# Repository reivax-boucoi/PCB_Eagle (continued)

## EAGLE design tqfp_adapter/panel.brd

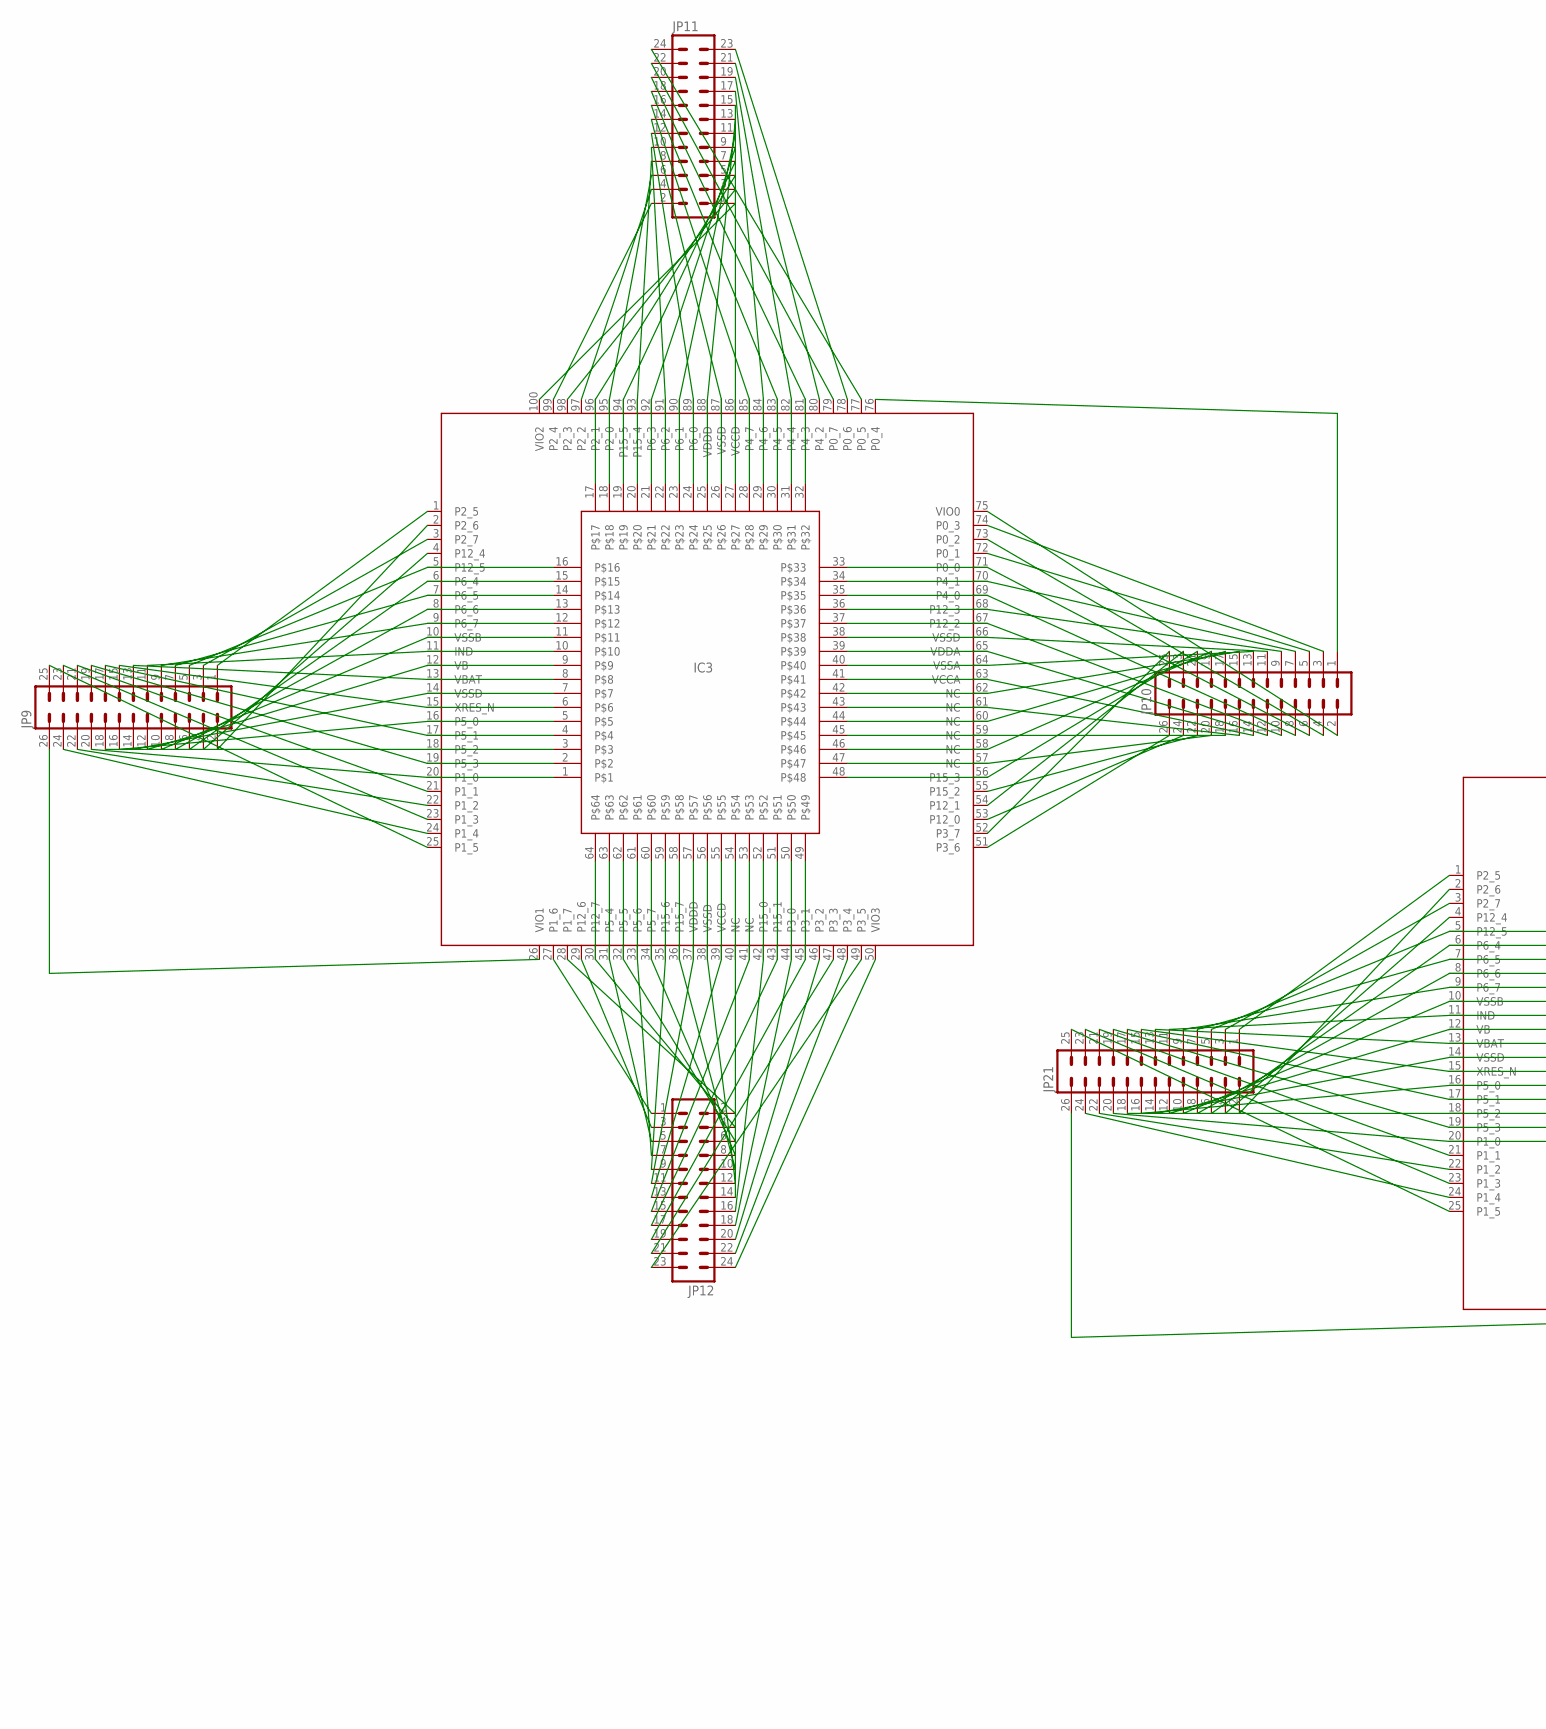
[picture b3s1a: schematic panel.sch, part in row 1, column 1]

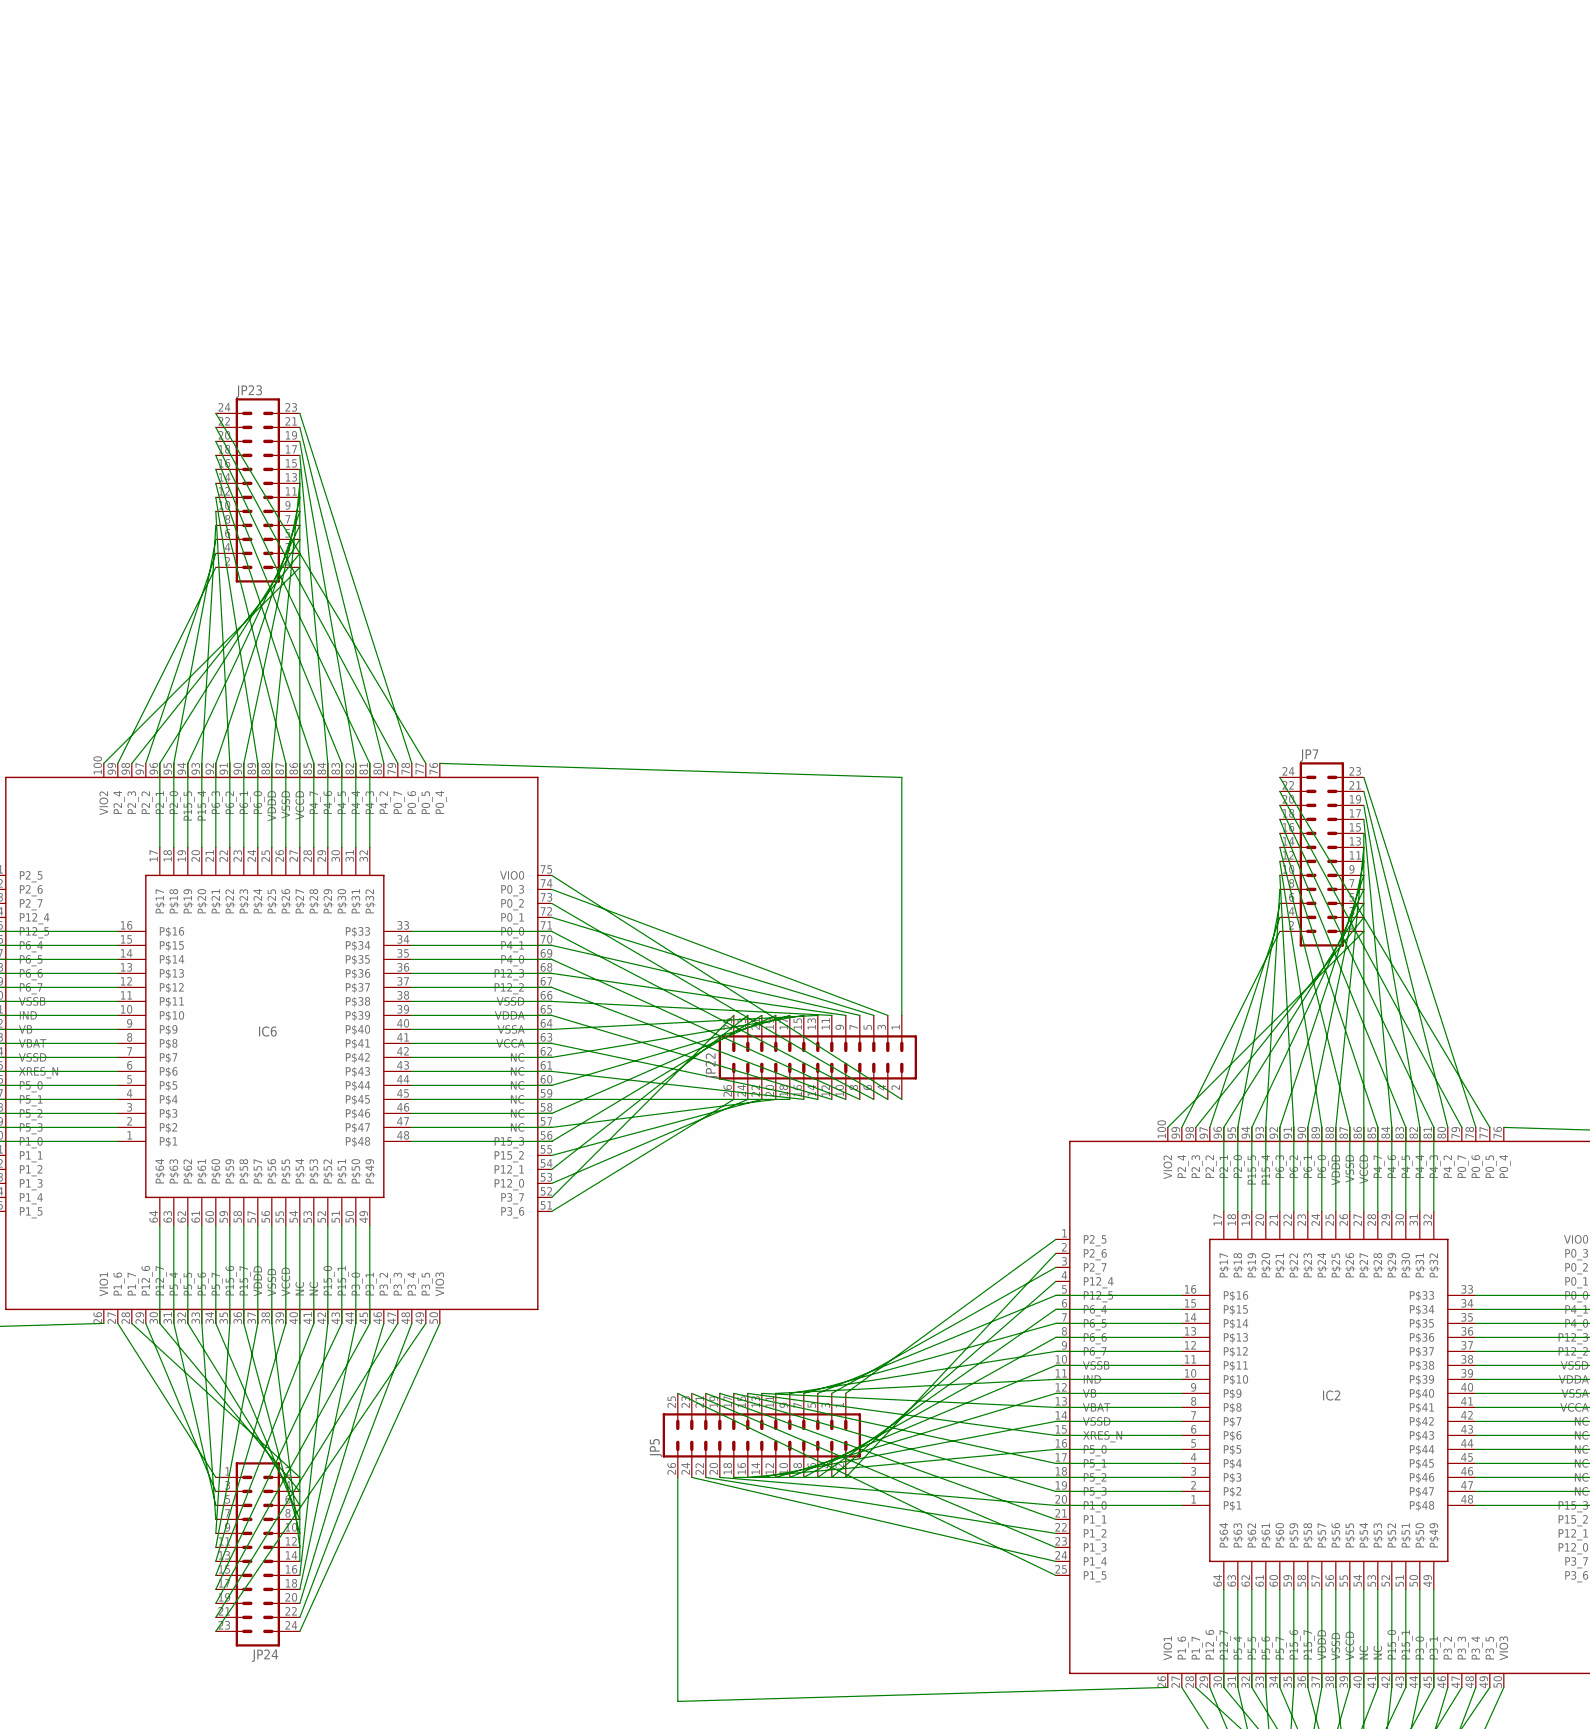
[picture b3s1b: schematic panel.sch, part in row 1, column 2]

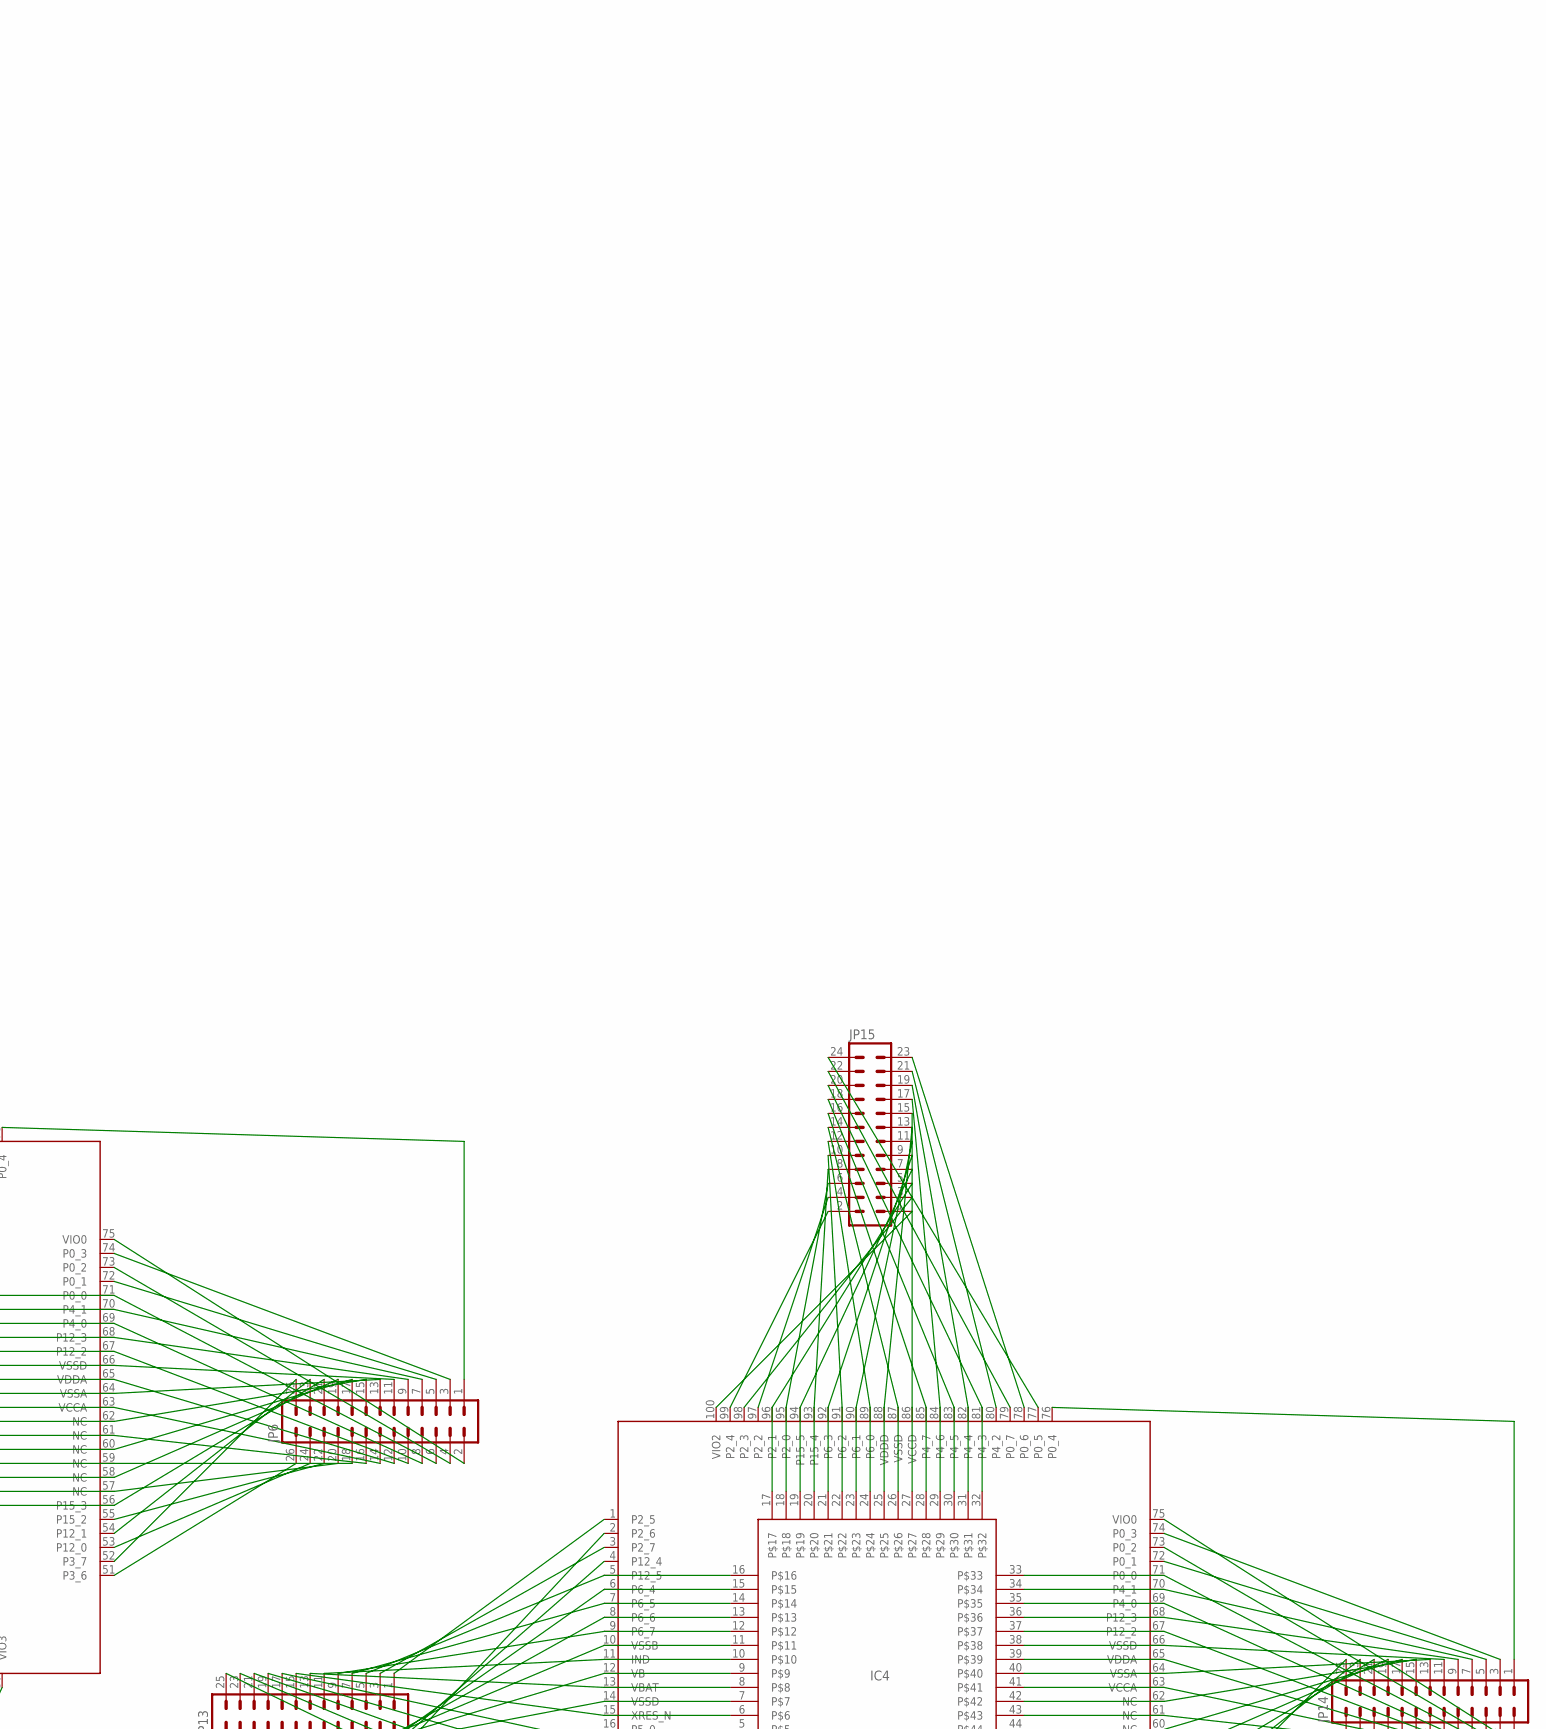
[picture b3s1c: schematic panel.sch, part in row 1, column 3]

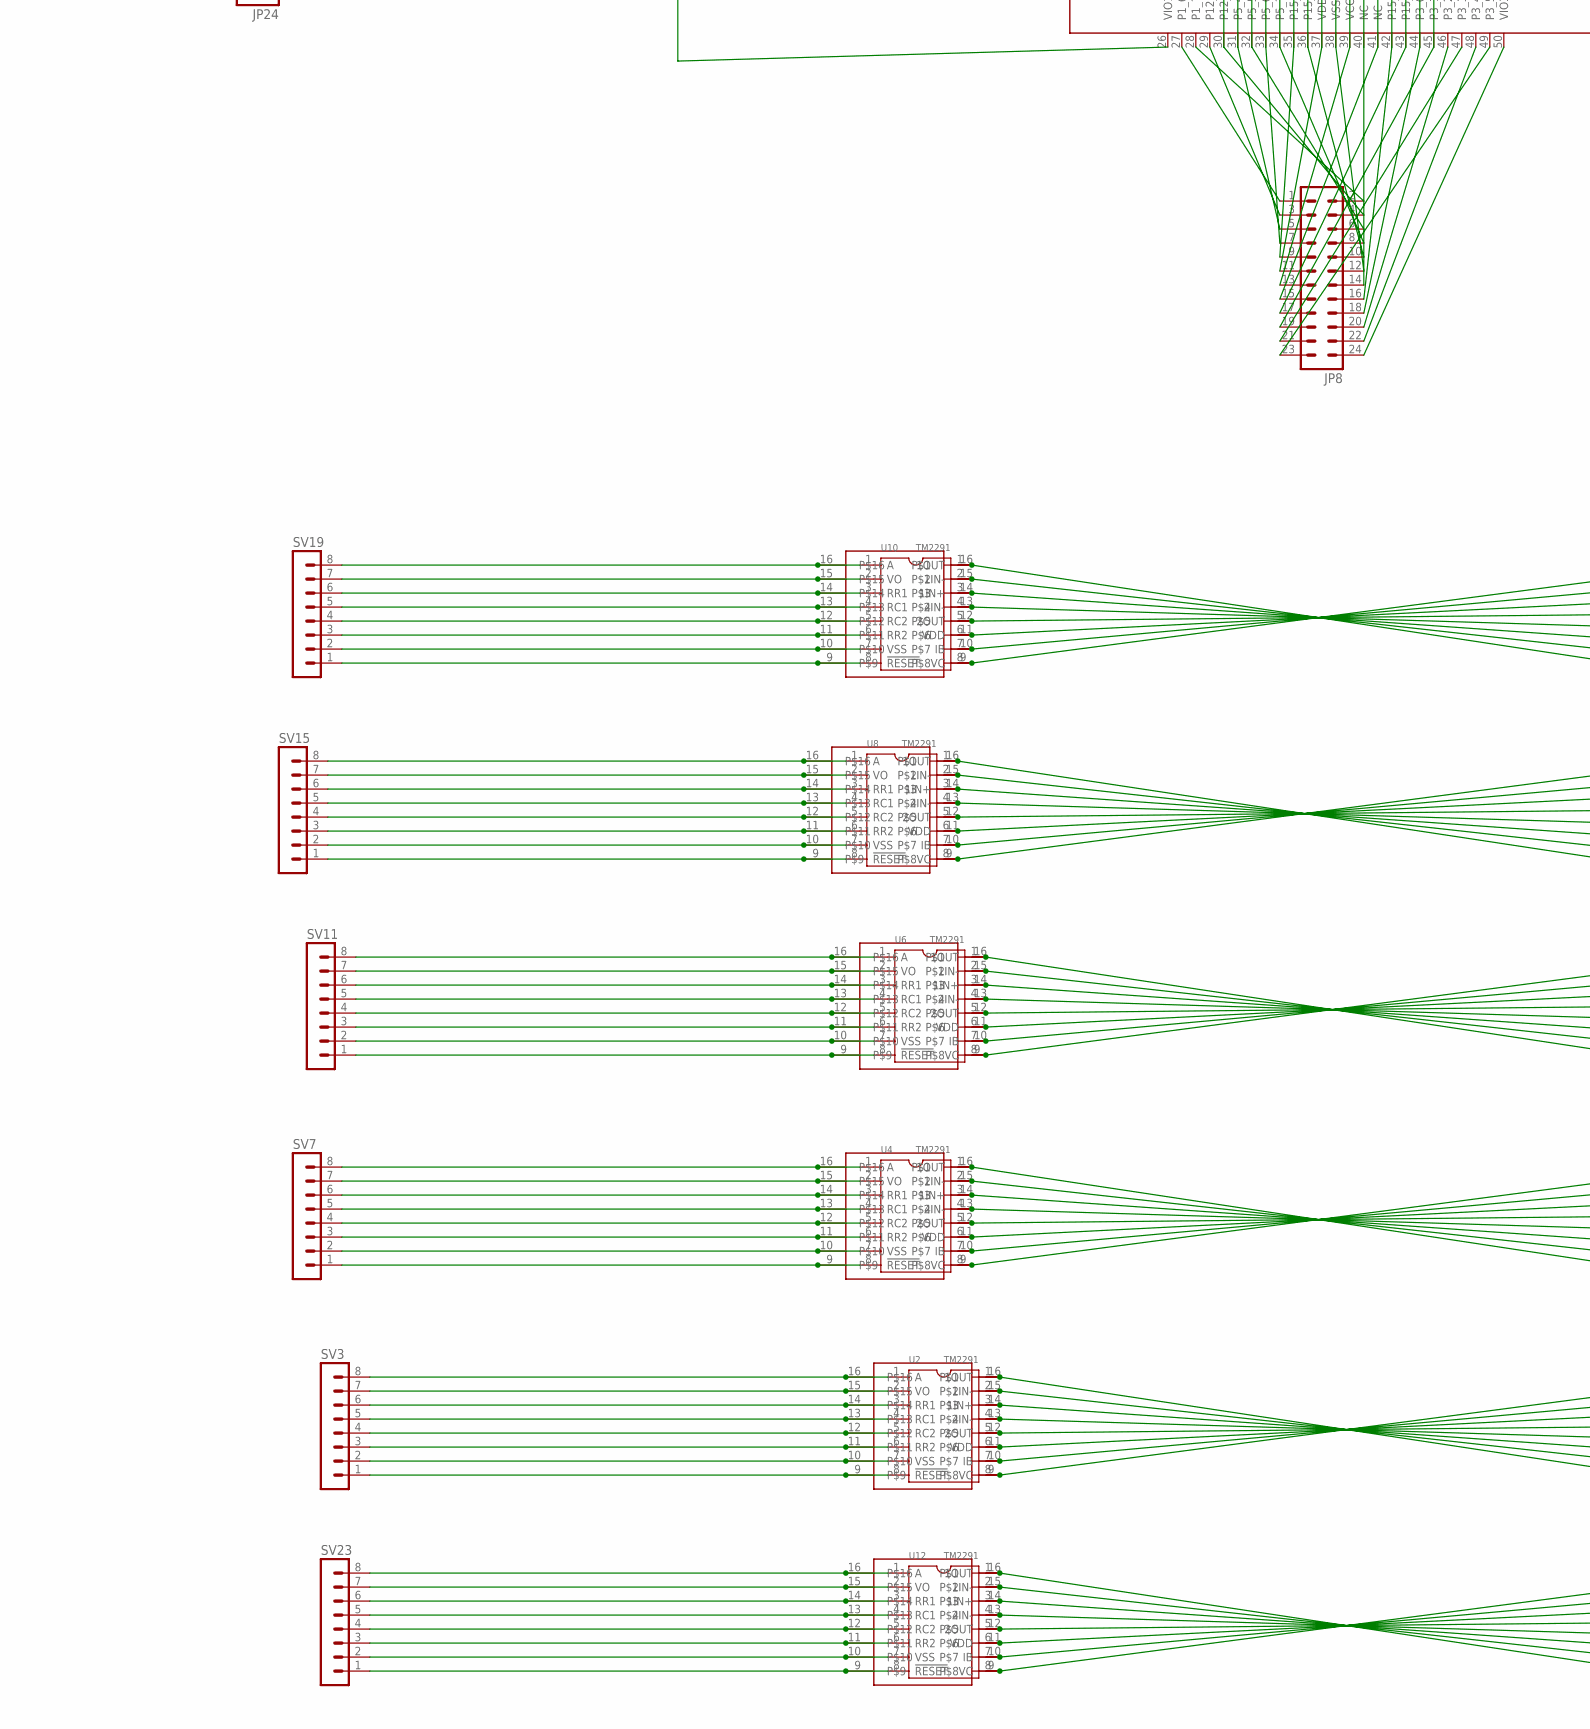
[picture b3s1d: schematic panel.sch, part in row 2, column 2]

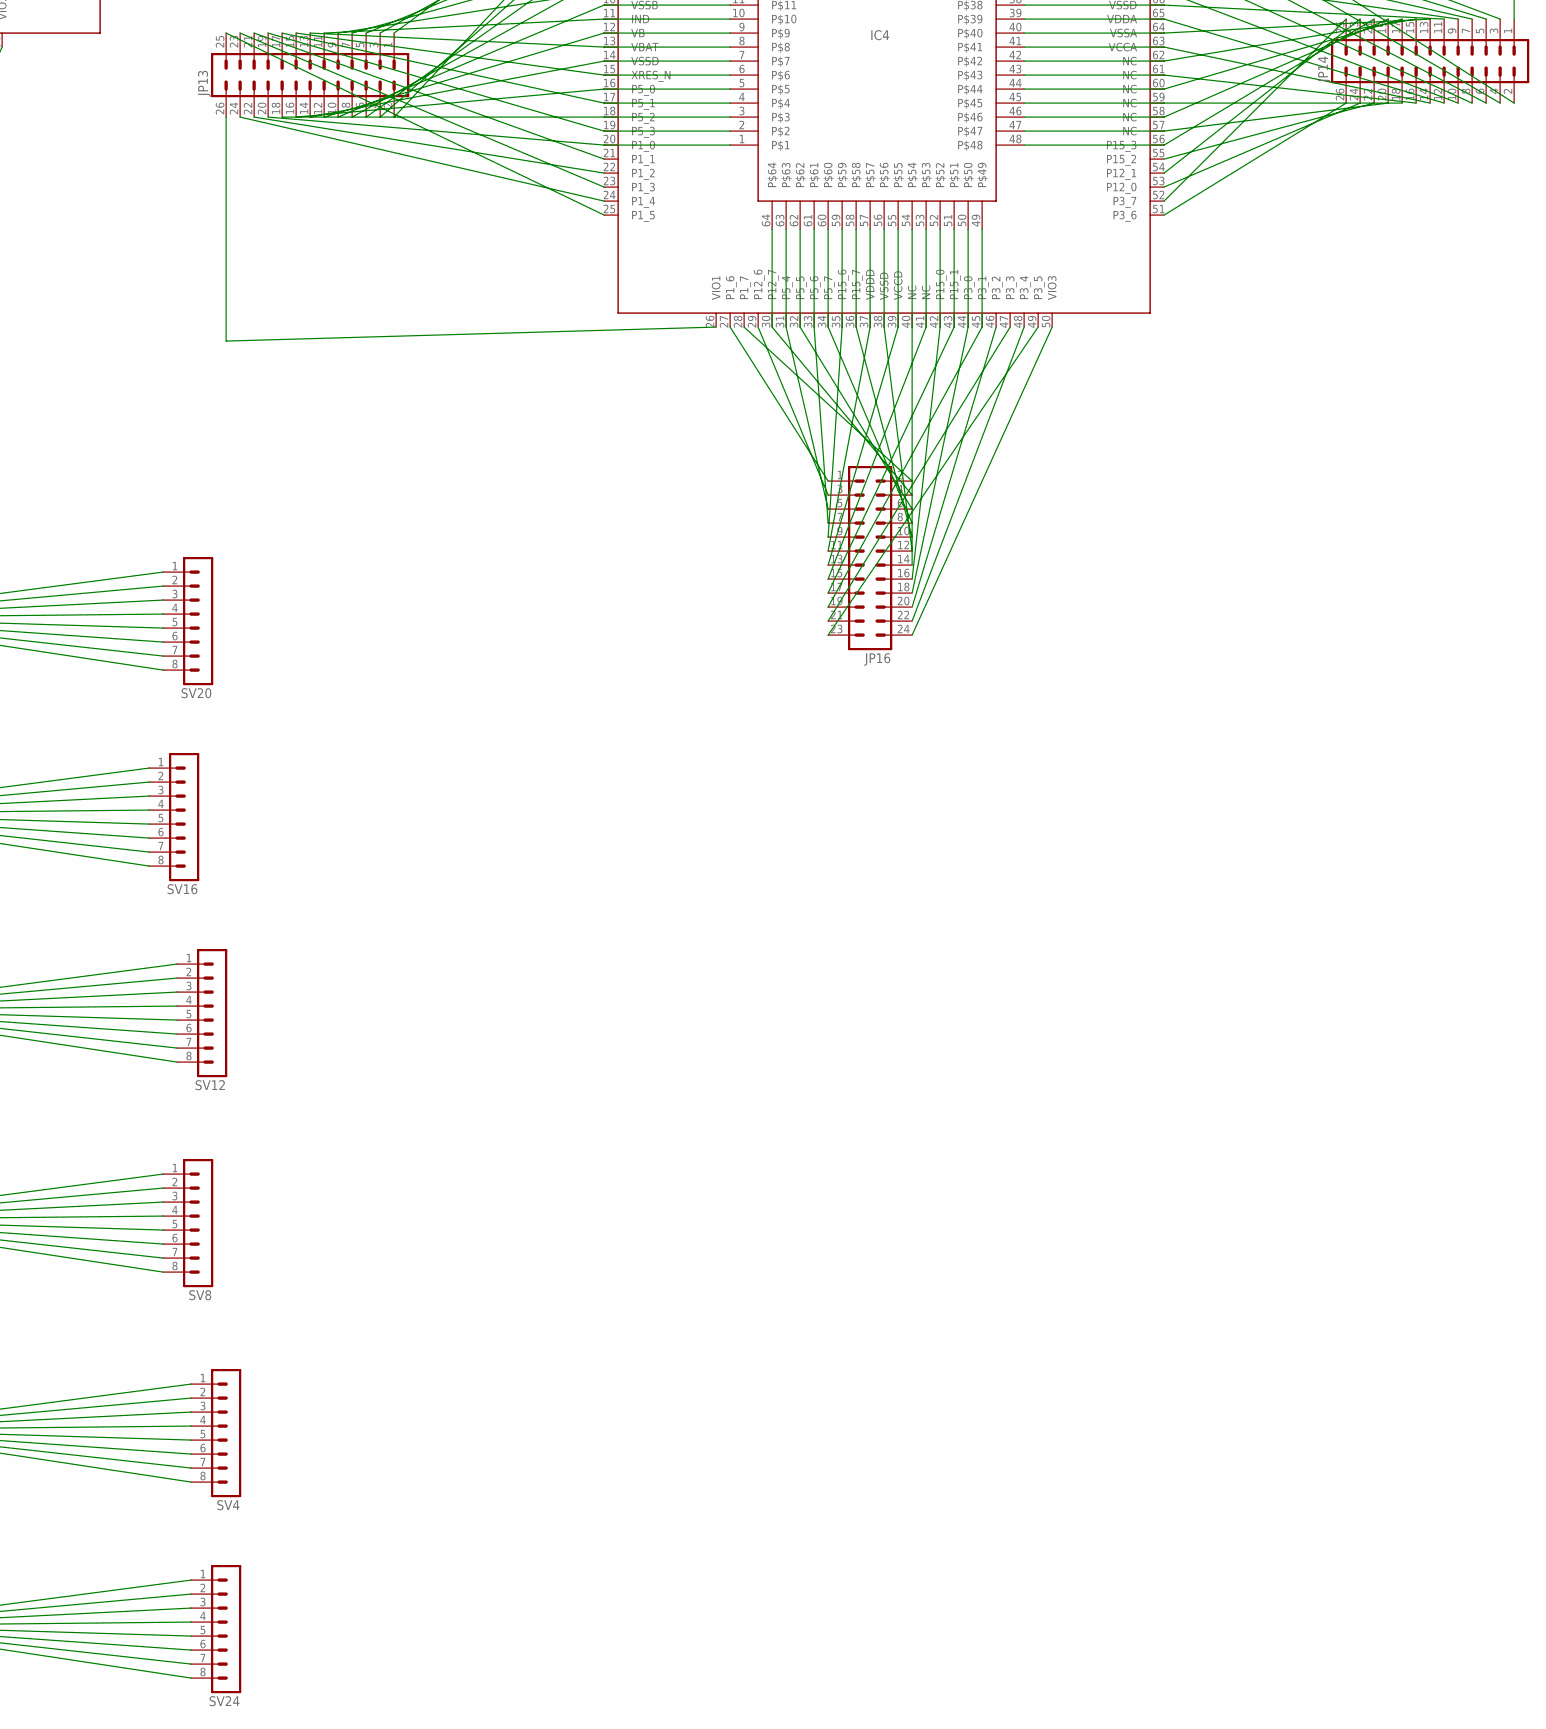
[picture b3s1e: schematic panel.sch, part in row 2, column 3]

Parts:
IC2, IC3, IC4, IC6: TQFP100-14X14
JP5, JP6, JP9, JP10, JP13, JP14, JP21, JP22: MA13-2
JP7, JP8, JP11, JP12, JP15, JP16, JP23, JP24: MA12-2
SV3, SV4, SV7, SV8, SV11, SV12, SV15, SV16, SV19, SV20, SV23, SV24: MA08-1
U2, U4, U6, U8, U10, U12: TM2291; SOP16-1.27-10.0X5.0MM
U$2, U$3, U$4, U$6: TQFP64; TQFP64-0.8
U$7, U$9, U$11, U$13, U$15, U$17: SSOP16; TSSOP16

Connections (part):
unnamed: IC2.1 (P2_5), JP5.1
unnamed: IC2.2 (P2_6), JP5.2
unnamed: IC2.3 (P2_7), JP5.3
unnamed: IC2.4 (P12_4), JP5.4
unnamed: IC2.5 (P12_5), JP5.5, U$2.16
unnamed: IC2.6 (P6_4), JP5.6, U$2.15
unnamed: IC2.7 (P6_5), JP5.7, U$2.14
unnamed: IC2.8 (P6_6), JP5.8, U$2.13
unnamed: IC2.9 (P6_7), JP5.9, U$2.12
unnamed: IC2.10 (VSSB), JP5.10, U$2.11
unnamed: IC2.11 (IND), JP5.11, U$2.10
unnamed: IC2.12 (VB), JP5.12, U$2.9
unnamed: IC2.13 (VBAT), JP5.13, U$2.8
unnamed: IC2.25 (P1_5), JP5.25
unnamed: IC2.24 (P1_4), JP5.24
unnamed: IC2.23 (P1_3), JP5.23
unnamed: IC2.22 (P1_2), JP5.22
unnamed: IC2.21 (P1_1), JP5.21
unnamed: IC2.20 (P1_0), JP5.20, U$2.1
unnamed: IC2.19 (P5_3), JP5.19, U$2.2
unnamed: IC2.18 (P5_2), JP5.18, U$2.3
unnamed: IC2.17 (P5_1), JP5.17, U$2.4
unnamed: IC2.16 (P5_0), JP5.16, U$2.5
unnamed: IC2.15 (XRES_N), JP5.15, U$2.6
unnamed: IC2.14 (VSSD), JP5.14, U$2.7
unnamed: IC2.27 (P1_6), JP8.1
unnamed: IC2.28 (P1_7), JP8.2
unnamed: IC2.29 (P12_6), JP8.3
unnamed: IC2.30 (P12_7), JP8.4, U$2.64
unnamed: IC2.31 (P5_4), JP8.5, U$2.63
unnamed: IC2.32 (P5_5), JP8.6, U$2.62
unnamed: IC2.33 (P5_6), JP8.7, U$2.61
unnamed: IC2.34 (P5_7), JP8.8, U$2.60
unnamed: IC2.35 (P15_6), JP8.9, U$2.59
unnamed: IC2.36 (P15_7), JP8.10, U$2.58
unnamed: IC2.37 (VDDD), JP8.11, U$2.57
unnamed: IC2.38 (VSSD), JP8.12, U$2.56
unnamed: IC2.50 (VIO3), JP8.24
unnamed: IC2.49 (P3_5), JP8.23
unnamed: IC2.48 (P3_4), JP8.22
unnamed: IC2.47 (P3_3), JP8.21
unnamed: IC2.46 (P3_2), JP8.20
unnamed: IC2.45 (P3_1), JP8.19, U$2.49
unnamed: IC2.44 (P3_0), JP8.18, U$2.50
unnamed: IC2.43 (P15_1), JP8.17, U$2.51
unnamed: IC2.42 (P15_0), JP8.16, U$2.52
unnamed: IC2.41 (NC), JP8.15, U$2.53
unnamed: IC2.40 (NC), JP8.14, U$2.54
unnamed: IC2.39 (VCCD), JP8.13, U$2.55
unnamed: IC2.63 (VCCA), JP6.14, U$2.41
unnamed: IC2.62 (NC), JP6.15, U$2.42
unnamed: IC2.61 (NC), JP6.16, U$2.43
unnamed: IC2.60 (NC), JP6.17, U$2.44
unnamed: IC2.59 (NC), JP6.18, U$2.45
unnamed: IC2.58 (NC), JP6.19, U$2.46
unnamed: IC2.57 (NC), JP6.20, U$2.47
unnamed: IC2.56 (P15_3), JP6.21, U$2.48
unnamed: IC2.55 (P15_2), JP6.22
unnamed: IC2.54 (P12_1), JP6.23
unnamed: IC2.53 (P12_0), JP6.24
unnamed: IC2.52 (P3_7), JP6.25
unnamed: IC2.51 (P3_6), JP6.26
unnamed: IC2.64 (VSSA), JP6.13, U$2.40
unnamed: IC2.65 (VDDA), JP6.12, U$2.39
unnamed: IC2.66 (VSSD), JP6.11, U$2.38
unnamed: IC2.67 (P12_2), JP6.10, U$2.37
unnamed: IC2.68 (P12_3), JP6.9, U$2.36
unnamed: IC2.69 (P4_0), JP6.8, U$2.35
unnamed: IC2.70 (P4_1), JP6.7, U$2.34
unnamed: IC2.71 (P0_0), JP6.6, U$2.33
unnamed: IC2.72 (P0_1), JP6.5
unnamed: IC2.73 (P0_2), JP6.4
unnamed: IC2.74 (P0_3), JP6.3
unnamed: IC2.75 (VIO0), JP6.2
unnamed: IC2.100 (VIO2), JP7.1
unnamed: IC2.99 (P2_4), JP7.2
unnamed: IC2.98 (P2_3), JP7.3
unnamed: IC2.97 (P2_2), JP7.4
unnamed: IC2.96 (P2_1), JP7.5, U$2.17
unnamed: IC2.95 (P2_0), JP7.6, U$2.18
unnamed: IC2.94 (P15_5), JP7.7, U$2.19
unnamed: IC2.93 (P15_4), JP7.8, U$2.20
unnamed: IC2.92 (P6_3), JP7.9, U$2.21
unnamed: IC2.91 (P6_2), JP7.10, U$2.22
unnamed: IC2.90 (P6_1), JP7.11, U$2.23
unnamed: IC2.89 (P6_0), JP7.12, U$2.24
unnamed: IC2.77 (P0_5), JP7.24
unnamed: IC2.78 (P0_6), JP7.23
unnamed: IC2.79 (P0_7), JP7.22
unnamed: IC2.80 (P4_2), JP7.21
unnamed: IC2.81 (P4_3), JP7.20, U$2.32
unnamed: IC2.82 (P4_4), JP7.19, U$2.31
unnamed: IC2.83 (P4_5), JP7.18, U$2.30
unnamed: IC2.84 (P4_6), JP7.17, U$2.29
unnamed: IC2.85 (P4_7), JP7.16, U$2.28
unnamed: IC2.86 (VCCD), JP7.15, U$2.27
unnamed: IC2.87 (VSSD), JP7.14, U$2.26
unnamed: IC2.88 (VDDD), JP7.13, U$2.25
unnamed: IC2.76 (P0_4), JP6.1
unnamed: IC2.26 (VIO1), JP5.26
unnamed: IC3.1 (P2_5), JP9.1
unnamed: IC3.2 (P2_6), JP9.2
unnamed: IC3.3 (P2_7), JP9.3
unnamed: IC3.4 (P12_4), JP9.4
unnamed: IC3.5 (P12_5), JP9.5, U$3.16
unnamed: IC3.6 (P6_4), JP9.6, U$3.15
unnamed: IC3.7 (P6_5), JP9.7, U$3.14
unnamed: IC3.8 (P6_6), JP9.8, U$3.13
unnamed: IC3.9 (P6_7), JP9.9, U$3.12
unnamed: IC3.10 (VSSB), JP9.10, U$3.11
unnamed: IC3.11 (IND), JP9.11, U$3.10
unnamed: IC3.12 (VB), JP9.12, U$3.9
unnamed: IC3.13 (VBAT), JP9.13, U$3.8
unnamed: IC3.25 (P1_5), JP9.25
unnamed: IC3.24 (P1_4), JP9.24
unnamed: IC3.23 (P1_3), JP9.23
unnamed: IC3.22 (P1_2), JP9.22
unnamed: IC3.21 (P1_1), JP9.21
unnamed: IC3.20 (P1_0), JP9.20, U$3.1
unnamed: IC3.19 (P5_3), JP9.19, U$3.2
unnamed: IC3.18 (P5_2), JP9.18, U$3.3
unnamed: IC3.17 (P5_1), JP9.17, U$3.4
unnamed: IC3.16 (P5_0), JP9.16, U$3.5
unnamed: IC3.15 (XRES_N), JP9.15, U$3.6
unnamed: IC3.14 (VSSD), JP9.14, U$3.7
unnamed: IC3.27 (P1_6), JP12.1
unnamed: IC3.28 (P1_7), JP12.2
unnamed: IC3.29 (P12_6), JP12.3
unnamed: IC3.30 (P12_7), JP12.4, U$3.64
unnamed: IC3.31 (P5_4), JP12.5, U$3.63
unnamed: IC3.32 (P5_5), JP12.6, U$3.62
unnamed: IC3.33 (P5_6), JP12.7, U$3.61
unnamed: IC3.34 (P5_7), JP12.8, U$3.60
unnamed: IC3.35 (P15_6), JP12.9, U$3.59
unnamed: IC3.36 (P15_7), JP12.10, U$3.58
unnamed: IC3.37 (VDDD), JP12.11, U$3.57
unnamed: IC3.38 (VSSD), JP12.12, U$3.56
unnamed: IC3.50 (VIO3), JP12.24
unnamed: IC3.49 (P3_5), JP12.23
unnamed: IC3.48 (P3_4), JP12.22
unnamed: IC3.47 (P3_3), JP12.21
unnamed: IC3.46 (P3_2), JP12.20
unnamed: IC3.45 (P3_1), JP12.19, U$3.49
unnamed: IC3.44 (P3_0), JP12.18, U$3.50
unnamed: IC3.43 (P15_1), JP12.17, U$3.51
unnamed: IC3.42 (P15_0), JP12.16, U$3.52
unnamed: IC3.41 (NC), JP12.15, U$3.53
unnamed: IC3.40 (NC), JP12.14, U$3.54
unnamed: IC3.39 (VCCD), JP12.13, U$3.55
unnamed: IC3.63 (VCCA), JP10.14, U$3.41
unnamed: IC3.62 (NC), JP10.15, U$3.42
unnamed: IC3.61 (NC), JP10.16, U$3.43
unnamed: IC3.60 (NC), JP10.17, U$3.44
unnamed: IC3.59 (NC), JP10.18, U$3.45
unnamed: IC3.58 (NC), JP10.19, U$3.46
unnamed: IC3.57 (NC), JP10.20, U$3.47
unnamed: IC3.56 (P15_3), JP10.21, U$3.48
unnamed: IC3.55 (P15_2), JP10.22
unnamed: IC3.54 (P12_1), JP10.23
unnamed: IC3.53 (P12_0), JP10.24
unnamed: IC3.52 (P3_7), JP10.25
unnamed: IC3.51 (P3_6), JP10.26
unnamed: IC3.64 (VSSA), JP10.13, U$3.40
unnamed: IC3.65 (VDDA), JP10.12, U$3.39
unnamed: IC3.66 (VSSD), JP10.11, U$3.38
unnamed: IC3.67 (P12_2), JP10.10, U$3.37
unnamed: IC3.68 (P12_3), JP10.9, U$3.36
unnamed: IC3.69 (P4_0), JP10.8, U$3.35
unnamed: IC3.70 (P4_1), JP10.7, U$3.34
unnamed: IC3.71 (P0_0), JP10.6, U$3.33
unnamed: IC3.72 (P0_1), JP10.5
unnamed: IC3.73 (P0_2), JP10.4
unnamed: IC3.74 (P0_3), JP10.3
unnamed: IC3.75 (VIO0), JP10.2
unnamed: IC3.100 (VIO2), JP11.1
unnamed: IC3.99 (P2_4), JP11.2
unnamed: IC3.98 (P2_3), JP11.3
unnamed: IC3.97 (P2_2), JP11.4
unnamed: IC3.96 (P2_1), JP11.5, U$3.17
unnamed: IC3.95 (P2_0), JP11.6, U$3.18
unnamed: IC3.94 (P15_5), JP11.7, U$3.19
unnamed: IC3.93 (P15_4), JP11.8, U$3.20
unnamed: IC3.92 (P6_3), JP11.9, U$3.21
unnamed: IC3.91 (P6_2), JP11.10, U$3.22
unnamed: IC3.90 (P6_1), JP11.11, U$3.23
unnamed: IC3.89 (P6_0), JP11.12, U$3.24
unnamed: IC3.77 (P0_5), JP11.24
unnamed: IC3.78 (P0_6), JP11.23
unnamed: IC3.79 (P0_7), JP11.22
unnamed: IC3.80 (P4_2), JP11.21
unnamed: IC3.81 (P4_3), JP11.20, U$3.32
unnamed: IC3.82 (P4_4), JP11.19, U$3.31
unnamed: IC3.83 (P4_5), JP11.18, U$3.30
unnamed: IC3.84 (P4_6), JP11.17, U$3.29
unnamed: IC3.85 (P4_7), JP11.16, U$3.28
unnamed: IC3.86 (VCCD), JP11.15, U$3.27
unnamed: IC3.87 (VSSD), JP11.14, U$3.26
unnamed: IC3.88 (VDDD), JP11.13, U$3.25
unnamed: IC3.76 (P0_4), JP10.1
unnamed: IC3.26 (VIO1), JP9.26
unnamed: IC4.1 (P2_5), JP13.1
unnamed: IC4.2 (P2_6), JP13.2
unnamed: IC4.3 (P2_7), JP13.3
unnamed: IC4.4 (P12_4), JP13.4
unnamed: IC4.5 (P12_5), JP13.5, U$4.16
unnamed: IC4.6 (P6_4), JP13.6, U$4.15
unnamed: IC4.7 (P6_5), JP13.7, U$4.14
unnamed: IC4.8 (P6_6), JP13.8, U$4.13
unnamed: IC4.9 (P6_7), JP13.9, U$4.12
unnamed: IC4.10 (VSSB), JP13.10, U$4.11
unnamed: IC4.11 (IND), JP13.11, U$4.10
unnamed: IC4.12 (VB), JP13.12, U$4.9
unnamed: IC4.13 (VBAT), JP13.13, U$4.8
unnamed: IC4.25 (P1_5), JP13.25
unnamed: IC4.24 (P1_4), JP13.24
unnamed: IC4.23 (P1_3), JP13.23
unnamed: IC4.22 (P1_2), JP13.22
unnamed: IC4.21 (P1_1), JP13.21
unnamed: IC4.20 (P1_0), JP13.20, U$4.1
unnamed: IC4.19 (P5_3), JP13.19, U$4.2
unnamed: IC4.18 (P5_2), JP13.18, U$4.3
unnamed: IC4.17 (P5_1), JP13.17, U$4.4
unnamed: IC4.16 (P5_0), JP13.16, U$4.5
unnamed: IC4.15 (XRES_N), JP13.15, U$4.6
unnamed: IC4.14 (VSSD), JP13.14, U$4.7
unnamed: IC4.27 (P1_6), JP16.1
unnamed: IC4.28 (P1_7), JP16.2
unnamed: IC4.29 (P12_6), JP16.3
unnamed: IC4.30 (P12_7), JP16.4, U$4.64
unnamed: IC4.31 (P5_4), JP16.5, U$4.63
unnamed: IC4.32 (P5_5), JP16.6, U$4.62
unnamed: IC4.33 (P5_6), JP16.7, U$4.61
unnamed: IC4.34 (P5_7), JP16.8, U$4.60
unnamed: IC4.35 (P15_6), JP16.9, U$4.59
unnamed: IC4.36 (P15_7), JP16.10, U$4.58
unnamed: IC4.37 (VDDD), JP16.11, U$4.57
unnamed: IC4.38 (VSSD), JP16.12, U$4.56
unnamed: IC4.50 (VIO3), JP16.24
unnamed: IC4.49 (P3_5), JP16.23
unnamed: IC4.48 (P3_4), JP16.22
unnamed: IC4.47 (P3_3), JP16.21
unnamed: IC4.46 (P3_2), JP16.20
unnamed: IC4.45 (P3_1), JP16.19, U$4.49
unnamed: IC4.44 (P3_0), JP16.18, U$4.50
unnamed: IC4.43 (P15_1), JP16.17, U$4.51
unnamed: IC4.42 (P15_0), JP16.16, U$4.52
unnamed: IC4.41 (NC), JP16.15, U$4.53
unnamed: IC4.40 (NC), JP16.14, U$4.54
unnamed: IC4.39 (VCCD), JP16.13, U$4.55
unnamed: IC4.63 (VCCA), JP14.14, U$4.41
unnamed: IC4.62 (NC), JP14.15, U$4.42
unnamed: IC4.61 (NC), JP14.16, U$4.43
unnamed: IC4.60 (NC), JP14.17, U$4.44
unnamed: IC4.59 (NC), JP14.18, U$4.45
unnamed: IC4.58 (NC), JP14.19, U$4.46
unnamed: IC4.57 (NC), JP14.20, U$4.47
unnamed: IC4.56 (P15_3), JP14.21, U$4.48
unnamed: IC4.55 (P15_2), JP14.22
unnamed: IC4.54 (P12_1), JP14.23
unnamed: IC4.53 (P12_0), JP14.24
unnamed: IC4.52 (P3_7), JP14.25
unnamed: IC4.51 (P3_6), JP14.26
unnamed: IC4.64 (VSSA), JP14.13, U$4.40
unnamed: IC4.65 (VDDA), JP14.12, U$4.39
unnamed: IC4.66 (VSSD), JP14.11, U$4.38
unnamed: IC4.67 (P12_2), JP14.10, U$4.37
unnamed: IC4.68 (P12_3), JP14.9, U$4.36
unnamed: IC4.69 (P4_0), JP14.8, U$4.35
unnamed: IC4.70 (P4_1), JP14.7, U$4.34
unnamed: IC4.71 (P0_0), JP14.6, U$4.33
unnamed: IC4.72 (P0_1), JP14.5
unnamed: IC4.73 (P0_2), JP14.4
unnamed: IC4.74 (P0_3), JP14.3
unnamed: IC4.75 (VIO0), JP14.2
unnamed: IC4.100 (VIO2), JP15.1
unnamed: IC4.99 (P2_4), JP15.2
unnamed: IC4.98 (P2_3), JP15.3
unnamed: IC4.97 (P2_2), JP15.4
unnamed: IC4.96 (P2_1), JP15.5, U$4.17
unnamed: IC4.95 (P2_0), JP15.6, U$4.18
unnamed: IC4.94 (P15_5), JP15.7, U$4.19
unnamed: IC4.93 (P15_4), JP15.8, U$4.20
unnamed: IC4.92 (P6_3), JP15.9, U$4.21
unnamed: IC4.91 (P6_2), JP15.10, U$4.22
unnamed: IC4.90 (P6_1), JP15.11, U$4.23
unnamed: IC4.89 (P6_0), JP15.12, U$4.24
unnamed: IC4.77 (P0_5), JP15.24
unnamed: IC4.78 (P0_6), JP15.23
unnamed: IC4.79 (P0_7), JP15.22
unnamed: IC4.80 (P4_2), JP15.21
unnamed: IC4.81 (P4_3), JP15.20, U$4.32
unnamed: IC4.82 (P4_4), JP15.19, U$4.31
unnamed: IC4.83 (P4_5), JP15.18, U$4.30
unnamed: IC4.84 (P4_6), JP15.17, U$4.29
unnamed: IC4.85 (P4_7), JP15.16, U$4.28
unnamed: IC4.86 (VCCD), JP15.15, U$4.27
unnamed: IC4.87 (VSSD), JP15.14, U$4.26
unnamed: IC4.88 (VDDD), JP15.13, U$4.25
unnamed: IC4.76 (P0_4), JP14.1
unnamed: IC4.26 (VIO1), JP13.26
unnamed: SV3.1, U2.8 (!RESET), U$7.9
unnamed: SV3.8, U2.1 (A), U$7.16
unnamed: SV3.5, U2.4 (RC1), U$7.13
unnamed: SV3.4, U2.5 (RC2), U$7.12
unnamed: SV3.6, U2.3 (RR1), U$7.14
unnamed: SV3.3, U2.6 (RR2), U$7.11
unnamed: SV3.7, U2.2 (VO), U$7.15
unnamed: SV4.8, U2.16 (1OUT), U$7.1
unnamed: SV4.7, U2.15 (1IN-), U$7.2
unnamed: SV4.6, U2.14 (1IN+), U$7.3
unnamed: SV4.5, U2.13 (2IN-), U$7.4
unnamed: SV4.4, U2.12 (2OUT), U$7.5
unnamed: SV4.2, U2.10 (IB), U$7.7
unnamed: SV4.1, U2.9 (VC), U$7.8
unnamed: SV7.1, U4.8 (!RESET), U$9.9
unnamed: SV7.8, U4.1 (A), U$9.16
unnamed: SV7.5, U4.4 (RC1), U$9.13
unnamed: SV7.4, U4.5 (RC2), U$9.12
unnamed: SV7.6, U4.3 (RR1), U$9.14
unnamed: SV7.3, U4.6 (RR2), U$9.11
unnamed: SV7.7, U4.2 (VO), U$9.15
unnamed: SV8.8, U4.16 (1OUT), U$9.1
unnamed: SV8.7, U4.15 (1IN-), U$9.2
unnamed: SV8.6, U4.14 (1IN+), U$9.3
unnamed: SV8.5, U4.13 (2IN-), U$9.4
unnamed: SV8.4, U4.12 (2OUT), U$9.5
unnamed: SV8.2, U4.10 (IB), U$9.7
unnamed: SV8.1, U4.9 (VC), U$9.8
unnamed: SV11.1, U6.8 (!RESET), U$11.9
unnamed: SV11.8, U6.1 (A), U$11.16
unnamed: SV11.5, U6.4 (RC1), U$11.13
unnamed: SV11.4, U6.5 (RC2), U$11.12
unnamed: SV11.6, U6.3 (RR1), U$11.14
unnamed: SV11.3, U6.6 (RR2), U$11.11
unnamed: SV11.7, U6.2 (VO), U$11.15
unnamed: SV12.8, U6.16 (1OUT), U$11.1
unnamed: SV12.7, U6.15 (1IN-), U$11.2
unnamed: SV12.6, U6.14 (1IN+), U$11.3
unnamed: SV12.5, U6.13 (2IN-), U$11.4
unnamed: SV12.4, U6.12 (2OUT), U$11.5
unnamed: SV12.2, U6.10 (IB), U$11.7
unnamed: SV12.1, U6.9 (VC), U$11.8
unnamed: SV15.1, U8.8 (!RESET), U$13.9
unnamed: SV15.8, U8.1 (A), U$13.16
unnamed: SV15.5, U8.4 (RC1), U$13.13
unnamed: SV15.4, U8.5 (RC2), U$13.12
unnamed: SV15.6, U8.3 (RR1), U$13.14
unnamed: SV15.3, U8.6 (RR2), U$13.11
unnamed: SV15.7, U8.2 (VO), U$13.15
unnamed: SV16.8, U8.16 (1OUT), U$13.1
unnamed: SV16.7, U8.15 (1IN-), U$13.2
unnamed: SV16.6, U8.14 (1IN+), U$13.3
unnamed: SV16.5, U8.13 (2IN-), U$13.4
unnamed: SV16.4, U8.12 (2OUT), U$13.5
unnamed: SV16.2, U8.10 (IB), U$13.7
unnamed: SV16.1, U8.9 (VC), U$13.8
unnamed: SV19.1, U10.8 (!RESET), U$15.9
unnamed: SV19.8, U10.1 (A), U$15.16
unnamed: SV19.5, U10.4 (RC1), U$15.13
unnamed: SV19.4, U10.5 (RC2), U$15.12
unnamed: SV19.6, U10.3 (RR1), U$15.14
unnamed: SV19.3, U10.6 (RR2), U$15.11
unnamed: SV19.7, U10.2 (VO), U$15.15
unnamed: SV20.8, U10.16 (1OUT), U$15.1
unnamed: SV20.7, U10.15 (1IN-), U$15.2
unnamed: SV20.6, U10.14 (1IN+), U$15.3
unnamed: SV20.5, U10.13 (2IN-), U$15.4
unnamed: SV20.4, U10.12 (2OUT), U$15.5
unnamed: SV20.2, U10.10 (IB), U$15.7
unnamed: SV20.1, U10.9 (VC), U$15.8
unnamed: SV23.1, U12.8 (!RESET), U$17.9
unnamed: SV23.8, U12.1 (A), U$17.16
unnamed: SV23.5, U12.4 (RC1), U$17.13
unnamed: SV23.4, U12.5 (RC2), U$17.12
unnamed: SV23.6, U12.3 (RR1), U$17.14
unnamed: SV23.3, U12.6 (RR2), U$17.11
unnamed: SV23.7, U12.2 (VO), U$17.15
unnamed: SV24.8, U12.16 (1OUT), U$17.1
unnamed: SV24.7, U12.15 (1IN-), U$17.2
unnamed: SV24.6, U12.14 (1IN+), U$17.3
unnamed: SV24.5, U12.13 (2IN-), U$17.4
unnamed: SV24.4, U12.12 (2OUT), U$17.5
unnamed: SV24.2, U12.10 (IB), U$17.7
unnamed: SV24.1, U12.9 (VC), U$17.8
unnamed: IC6.1 (P2_5), JP21.1
unnamed: IC6.2 (P2_6), JP21.2
unnamed: IC6.3 (P2_7), JP21.3
unnamed: IC6.4 (P12_4), JP21.4
unnamed: IC6.5 (P12_5), JP21.5, U$6.16
unnamed: IC6.6 (P6_4), JP21.6, U$6.15
unnamed: IC6.7 (P6_5), JP21.7, U$6.14
unnamed: IC6.8 (P6_6), JP21.8, U$6.13
unnamed: IC6.9 (P6_7), JP21.9, U$6.12
unnamed: IC6.10 (VSSB), JP21.10, U$6.11
unnamed: IC6.11 (IND), JP21.11, U$6.10
unnamed: IC6.12 (VB), JP21.12, U$6.9
unnamed: IC6.13 (VBAT), JP21.13, U$6.8
unnamed: IC6.25 (P1_5), JP21.25
unnamed: IC6.24 (P1_4), JP21.24
unnamed: IC6.23 (P1_3), JP21.23
unnamed: IC6.22 (P1_2), JP21.22
unnamed: IC6.21 (P1_1), JP21.21
unnamed: IC6.20 (P1_0), JP21.20, U$6.1
unnamed: IC6.19 (P5_3), JP21.19, U$6.2
unnamed: IC6.18 (P5_2), JP21.18, U$6.3
unnamed: IC6.17 (P5_1), JP21.17, U$6.4
unnamed: IC6.16 (P5_0), JP21.16, U$6.5
unnamed: IC6.15 (XRES_N), JP21.15, U$6.6
unnamed: IC6.14 (VSSD), JP21.14, U$6.7
unnamed: IC6.27 (P1_6), JP24.1
unnamed: IC6.28 (P1_7), JP24.2
unnamed: IC6.29 (P12_6), JP24.3
unnamed: IC6.30 (P12_7), JP24.4, U$6.64
unnamed: IC6.31 (P5_4), JP24.5, U$6.63
unnamed: IC6.32 (P5_5), JP24.6, U$6.62
unnamed: IC6.33 (P5_6), JP24.7, U$6.61
unnamed: IC6.34 (P5_7), JP24.8, U$6.60
unnamed: IC6.35 (P15_6), JP24.9, U$6.59
unnamed: IC6.36 (P15_7), JP24.10, U$6.58
unnamed: IC6.37 (VDDD), JP24.11, U$6.57
unnamed: IC6.38 (VSSD), JP24.12, U$6.56
unnamed: IC6.50 (VIO3), JP24.24
unnamed: IC6.49 (P3_5), JP24.23
unnamed: IC6.48 (P3_4), JP24.22
unnamed: IC6.47 (P3_3), JP24.21
unnamed: IC6.46 (P3_2), JP24.20
unnamed: IC6.45 (P3_1), JP24.19, U$6.49
unnamed: IC6.44 (P3_0), JP24.18, U$6.50
unnamed: IC6.43 (P15_1), JP24.17, U$6.51
unnamed: IC6.42 (P15_0), JP24.16, U$6.52
unnamed: IC6.41 (NC), JP24.15, U$6.53
unnamed: IC6.40 (NC), JP24.14, U$6.54
unnamed: IC6.39 (VCCD), JP24.13, U$6.55
unnamed: IC6.63 (VCCA), JP22.14, U$6.41
unnamed: IC6.62 (NC), JP22.15, U$6.42
unnamed: IC6.61 (NC), JP22.16, U$6.43
unnamed: IC6.60 (NC), JP22.17, U$6.44
unnamed: IC6.59 (NC), JP22.18, U$6.45
unnamed: IC6.58 (NC), JP22.19, U$6.46
unnamed: IC6.57 (NC), JP22.20, U$6.47
unnamed: IC6.56 (P15_3), JP22.21, U$6.48
unnamed: IC6.55 (P15_2), JP22.22
unnamed: IC6.54 (P12_1), JP22.23
unnamed: IC6.53 (P12_0), JP22.24
unnamed: IC6.52 (P3_7), JP22.25
unnamed: IC6.51 (P3_6), JP22.26
unnamed: IC6.64 (VSSA), JP22.13, U$6.40
unnamed: IC6.65 (VDDA), JP22.12, U$6.39
unnamed: IC6.66 (VSSD), JP22.11, U$6.38
unnamed: IC6.67 (P12_2), JP22.10, U$6.37
unnamed: IC6.68 (P12_3), JP22.9, U$6.36
unnamed: IC6.69 (P4_0), JP22.8, U$6.35
unnamed: IC6.70 (P4_1), JP22.7, U$6.34
unnamed: IC6.71 (P0_0), JP22.6, U$6.33
unnamed: IC6.72 (P0_1), JP22.5
unnamed: IC6.73 (P0_2), JP22.4
unnamed: IC6.74 (P0_3), JP22.3
unnamed: IC6.75 (VIO0), JP22.2
unnamed: IC6.100 (VIO2), JP23.1
unnamed: IC6.99 (P2_4), JP23.2
unnamed: IC6.98 (P2_3), JP23.3
unnamed: IC6.97 (P2_2), JP23.4
unnamed: IC6.96 (P2_1), JP23.5, U$6.17
unnamed: IC6.95 (P2_0), JP23.6, U$6.18
unnamed: IC6.94 (P15_5), JP23.7, U$6.19
unnamed: IC6.93 (P15_4), JP23.8, U$6.20
unnamed: IC6.92 (P6_3), JP23.9, U$6.21
unnamed: IC6.91 (P6_2), JP23.10, U$6.22
unnamed: IC6.90 (P6_1), JP23.11, U$6.23
unnamed: IC6.89 (P6_0), JP23.12, U$6.24
unnamed: IC6.77 (P0_5), JP23.24
unnamed: IC6.78 (P0_6), JP23.23
unnamed: IC6.79 (P0_7), JP23.22
unnamed: IC6.80 (P4_2), JP23.21
unnamed: IC6.81 (P4_3), JP23.20, U$6.32
unnamed: IC6.82 (P4_4), JP23.19, U$6.31
unnamed: IC6.83 (P4_5), JP23.18, U$6.30
unnamed: IC6.84 (P4_6), JP23.17, U$6.29
unnamed: IC6.85 (P4_7), JP23.16, U$6.28
unnamed: IC6.86 (VCCD), JP23.15, U$6.27
unnamed: IC6.87 (VSSD), JP23.14, U$6.26
unnamed: IC6.88 (VDDD), JP23.13, U$6.25
unnamed: IC6.76 (P0_4), JP22.1
unnamed: IC6.26 (VIO1), JP21.26
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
